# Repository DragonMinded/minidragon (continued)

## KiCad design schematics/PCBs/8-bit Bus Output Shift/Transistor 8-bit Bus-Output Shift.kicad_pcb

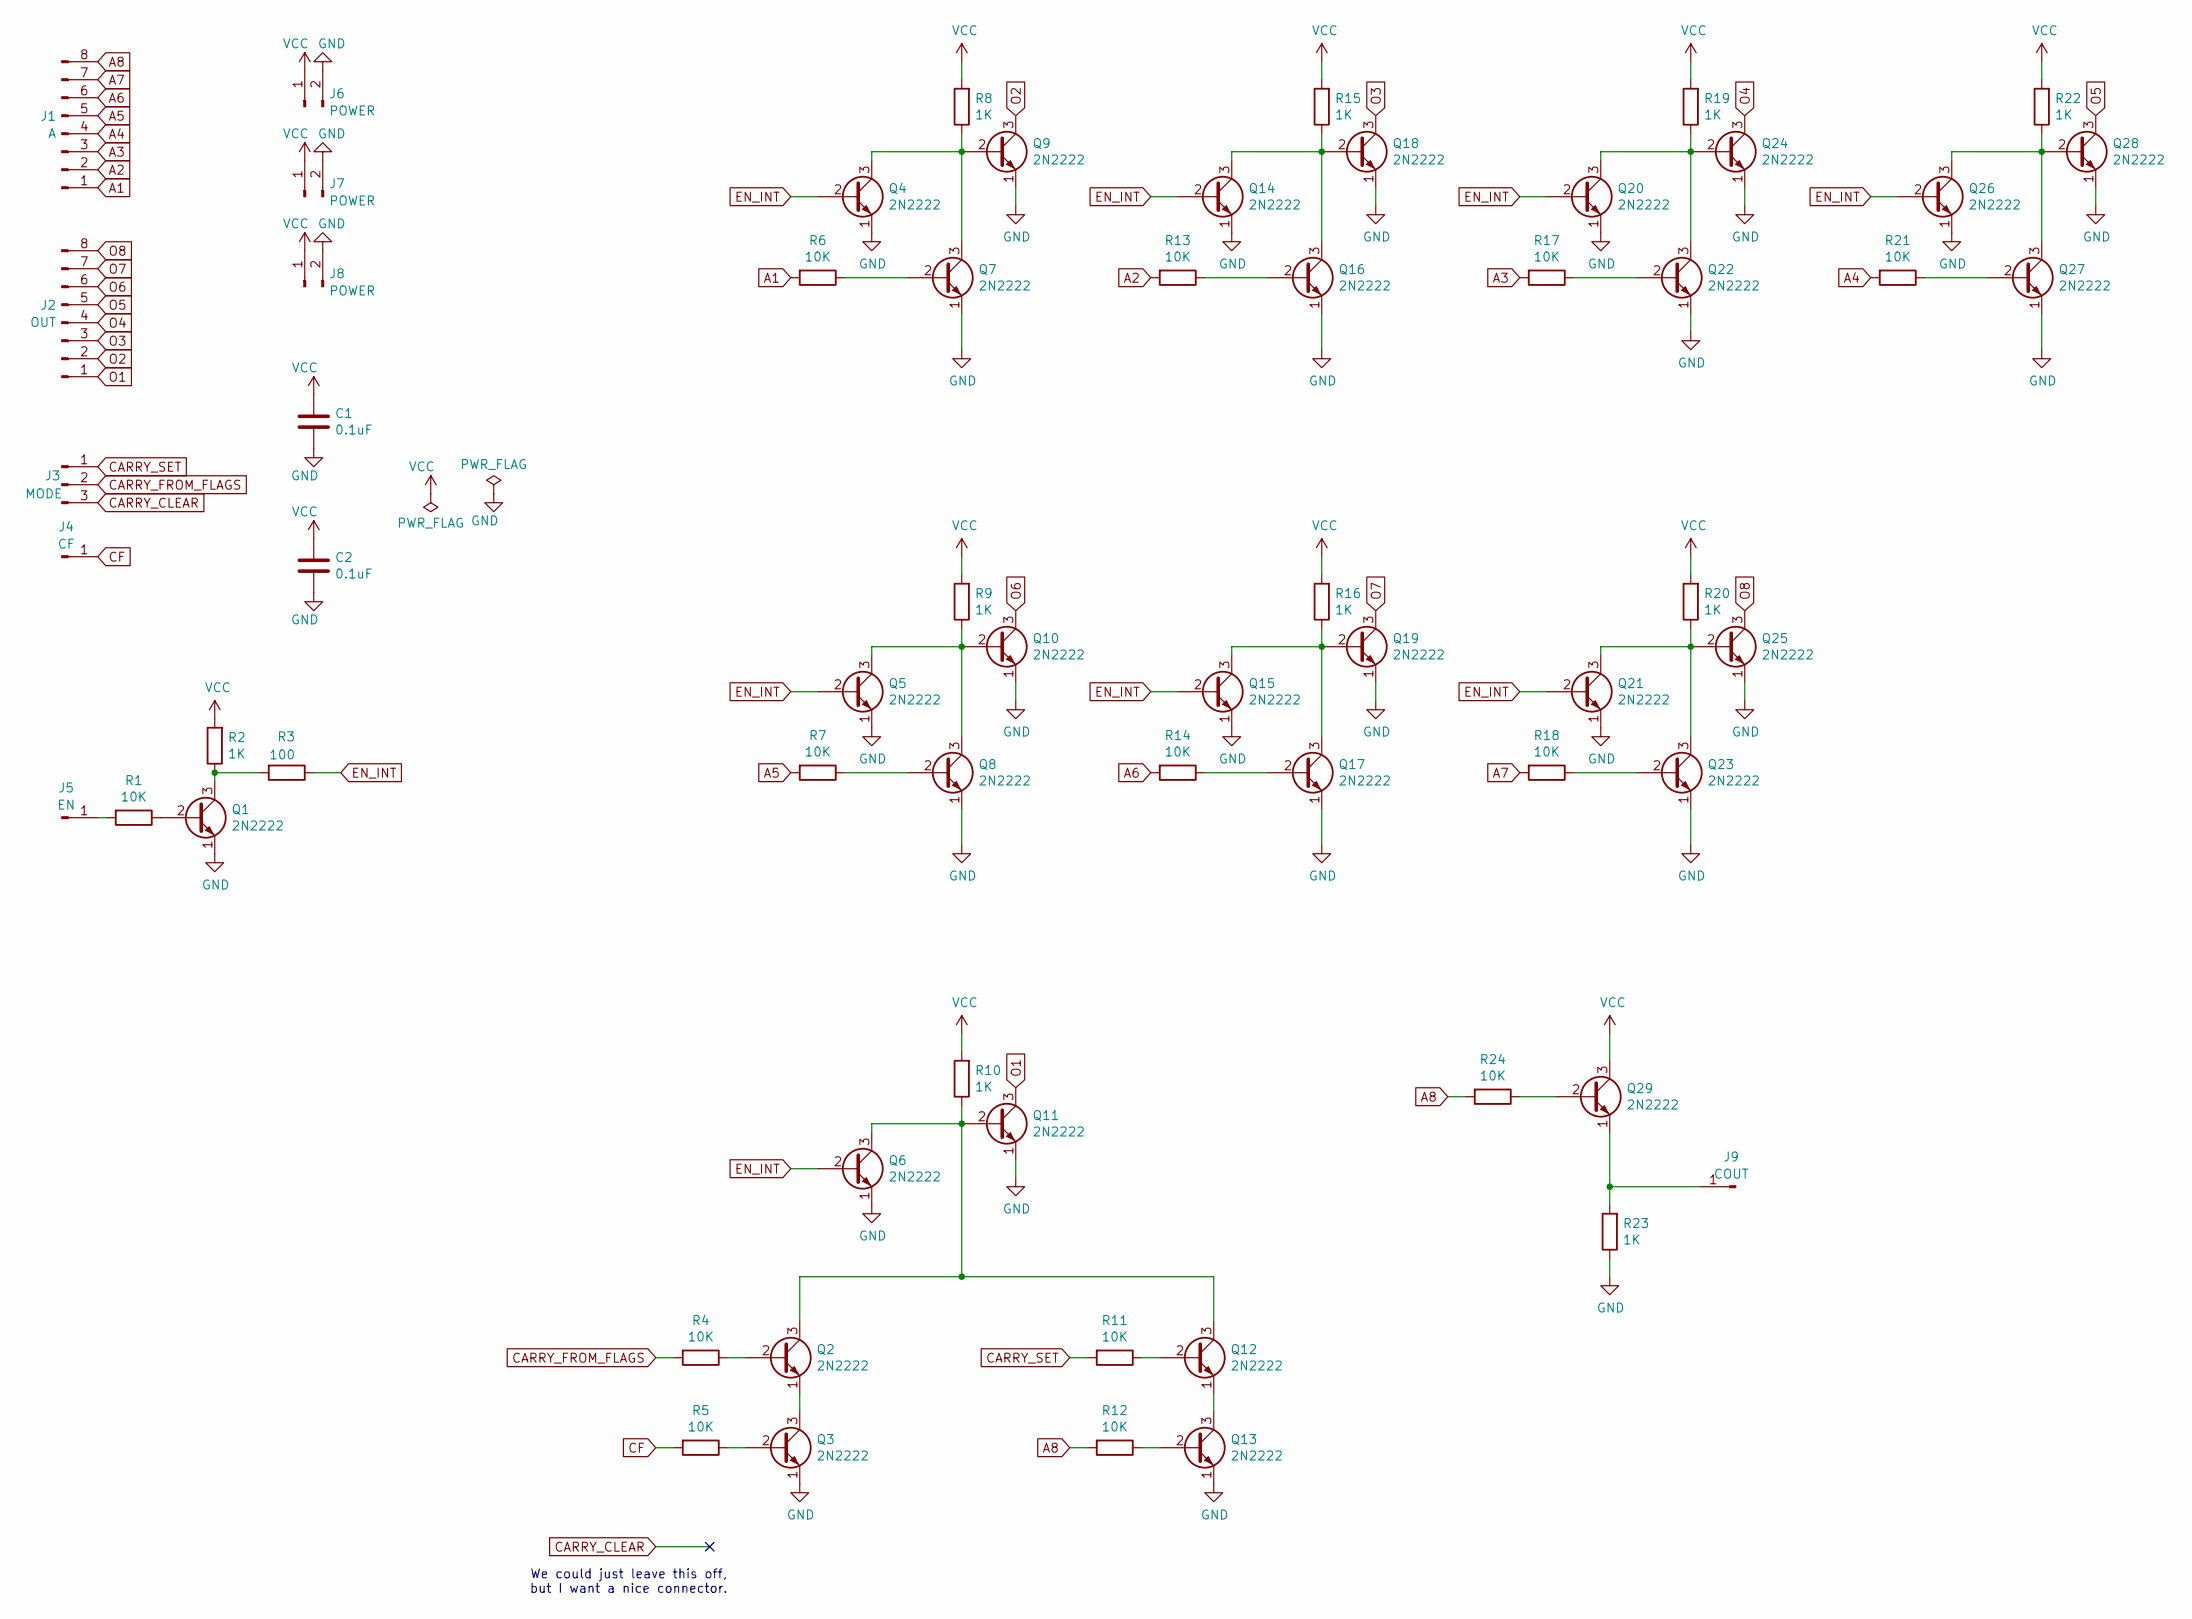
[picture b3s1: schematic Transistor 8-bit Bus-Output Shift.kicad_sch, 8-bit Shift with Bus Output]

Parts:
C1, C2: 0.1uF; C_Disc_D4.3mm_W1.9mm_P5.00mm
J1: A; PinHeader_1x08_P2.54mm_Vertical
J2: OUT; PinHeader_1x08_P2.54mm_Vertical
J3: MODE; PinHeader_1x03_P2.54mm_Vertical
J4: CF; PinHeader_1x01_P2.54mm_Vertical
J5: EN; PinHeader_1x01_P2.54mm_Vertical
J6, J7, J8: POWER; PinHeader_1x02_P2.54mm_Vertical
J9: COUT; PinHeader_1x01_P2.54mm_Vertical
Q1, Q2, Q3, Q4, Q5, Q6, Q7, Q8, Q9, Q10, Q11, Q12, Q13, Q14, Q15, Q16, Q17, Q18, Q19, Q20, Q21, Q22, Q23, Q24, Q25, Q26, Q27, Q28, Q29: 2N2222; TO-92_Inline
R1, R4, R5, R6, R7, R11, R12, R13, R14, R17, R18, R21, R24: 10K; R_Axial_DIN0309_L9.0mm_D3.2mm_P12.70mm_Horizontal
R2, R8, R9, R10, R15, R16, R19, R20, R22, R23: 1K; R_Axial_DIN0309_L9.0mm_D3.2mm_P12.70mm_Horizontal
R3: 100; R_Axial_DIN0309_L9.0mm_D3.2mm_P12.70mm_Horizontal

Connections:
A1: J1.1, R6.2
A2: J1.2, R13.2
A3: J1.3, R17.2
A4: J1.4, R21.2
A5: J1.5, R7.2
A6: J1.6, R14.2
A7: J1.7, R18.2
A8: J1.8, R12.2, R24.2
CARRY_CLEAR: J3.3
CARRY_FROM_FLAGS: J3.2, R4.2
CARRY_SET: J3.1, R11.2
CF: J4.1, R5.2
EN_INT: Q4.2 (B), Q5.2 (B), Q6.2 (B), Q14.2 (B), Q15.2 (B), Q20.2 (B), Q21.2 (B), Q26.2 (B), R3.1
GND: C1.2, C2.2, J6.2, J7.2, J8.2, Q1.1 (E), Q3.1 (E), Q4.1 (E), Q5.1 (E), Q6.1 (E), Q7.1 (E), Q8.1 (E), Q9.1 (E), Q10.1 (E), Q11.1 (E), Q13.1 (E), Q14.1 (E), Q15.1 (E), Q16.1 (E), Q17.1 (E), Q18.1 (E), Q19.1 (E), Q20.1 (E), Q21.1 (E), Q22.1 (E), Q23.1 (E), Q24.1 (E), Q25.1 (E), Q26.1 (E), Q27.1 (E), Q28.1 (E), R23.1
unnamed: J5.1, R1.2
unnamed: J9.1, Q29.1 (E), R23.2
unnamed: Q1.2 (B), R1.1
unnamed: Q1.3 (C), R2.1, R3.2
unnamed: Q2.2 (B), R4.1
unnamed: Q2.1 (E), Q3.3 (C)
unnamed: Q3.2 (B), R5.1
unnamed: Q4.3 (C), Q7.3 (C), Q9.2 (B), R8.1
unnamed: Q7.2 (B), R6.1
unnamed: Q8.2 (B), R7.1
unnamed: Q5.3 (C), Q8.3 (C), Q10.2 (B), R9.1
unnamed: Q2.3 (C), Q6.3 (C), Q11.2 (B), Q12.3 (C), R10.1
unnamed: Q12.2 (B), R11.1
unnamed: Q12.1 (E), Q13.3 (C)
unnamed: Q13.2 (B), R12.1
unnamed: Q14.3 (C), Q16.3 (C), Q18.2 (B), R15.1
unnamed: Q15.3 (C), Q17.3 (C), Q19.2 (B), R16.1
unnamed: Q16.2 (B), R13.1
unnamed: Q17.2 (B), R14.1
unnamed: Q20.3 (C), Q22.3 (C), Q24.2 (B), R19.1
unnamed: Q21.3 (C), Q23.3 (C), Q25.2 (B), R20.1
unnamed: Q22.2 (B), R17.1
unnamed: Q23.2 (B), R18.1
unnamed: Q26.3 (C), Q27.3 (C), Q28.2 (B), R22.1
unnamed: Q27.2 (B), R21.1
unnamed: Q29.2 (B), R24.1
O1: J2.1, Q11.3 (C)
O2: J2.2, Q9.3 (C)
O3: J2.3, Q18.3 (C)
O4: J2.4, Q24.3 (C)
O5: J2.5, Q28.3 (C)
O6: J2.6, Q10.3 (C)
O7: J2.7, Q19.3 (C)
O8: J2.8, Q25.3 (C)
VCC: C1.1, C2.1, J6.1, J7.1, J8.1, Q29.3 (C), R2.2, R8.2, R9.2, R10.2, R15.2, R16.2, R19.2, R20.2, R22.2

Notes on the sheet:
We could just leave this off, but I want a nice connector.

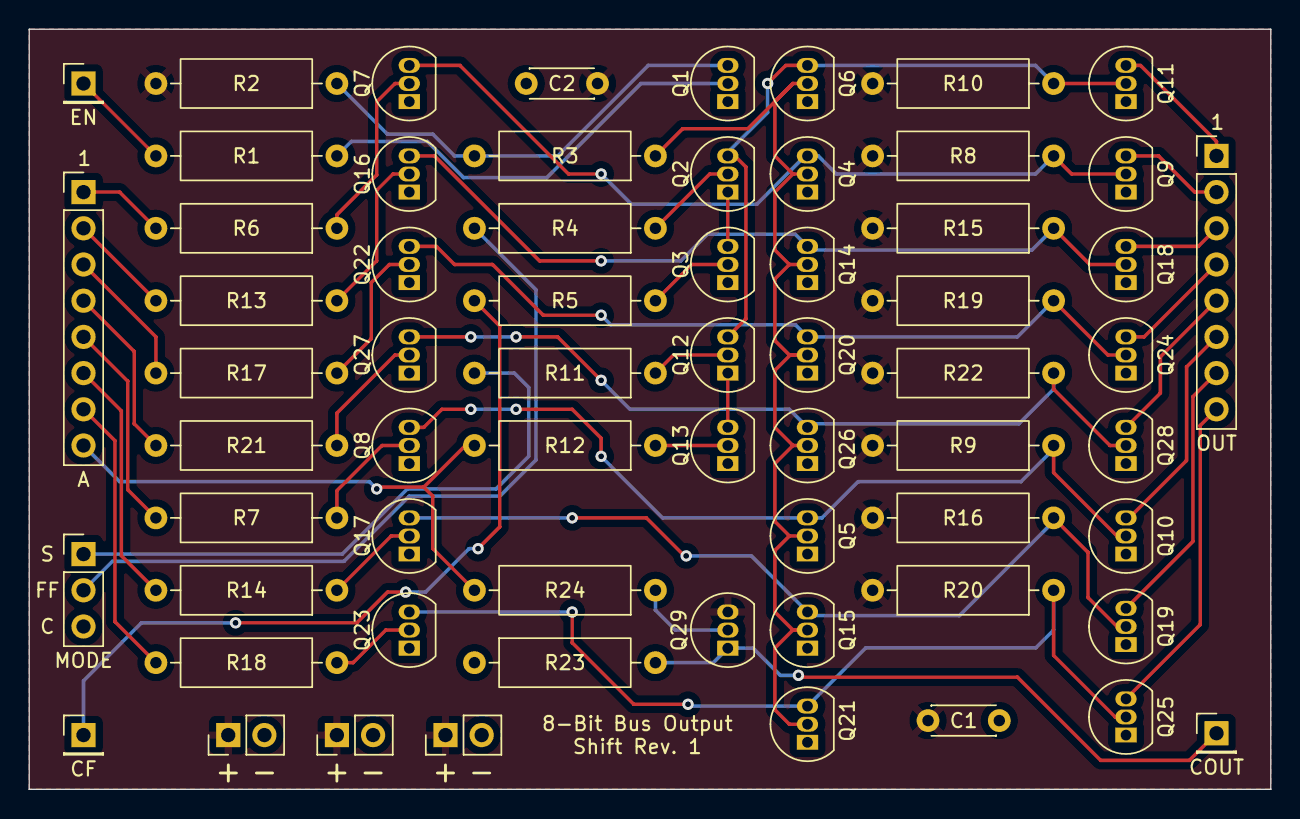
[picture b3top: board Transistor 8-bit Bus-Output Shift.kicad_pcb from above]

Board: 2 copper layers, 87.1 x 53.3 mm, 64 parts (0 on the bottom side), 48 nets.

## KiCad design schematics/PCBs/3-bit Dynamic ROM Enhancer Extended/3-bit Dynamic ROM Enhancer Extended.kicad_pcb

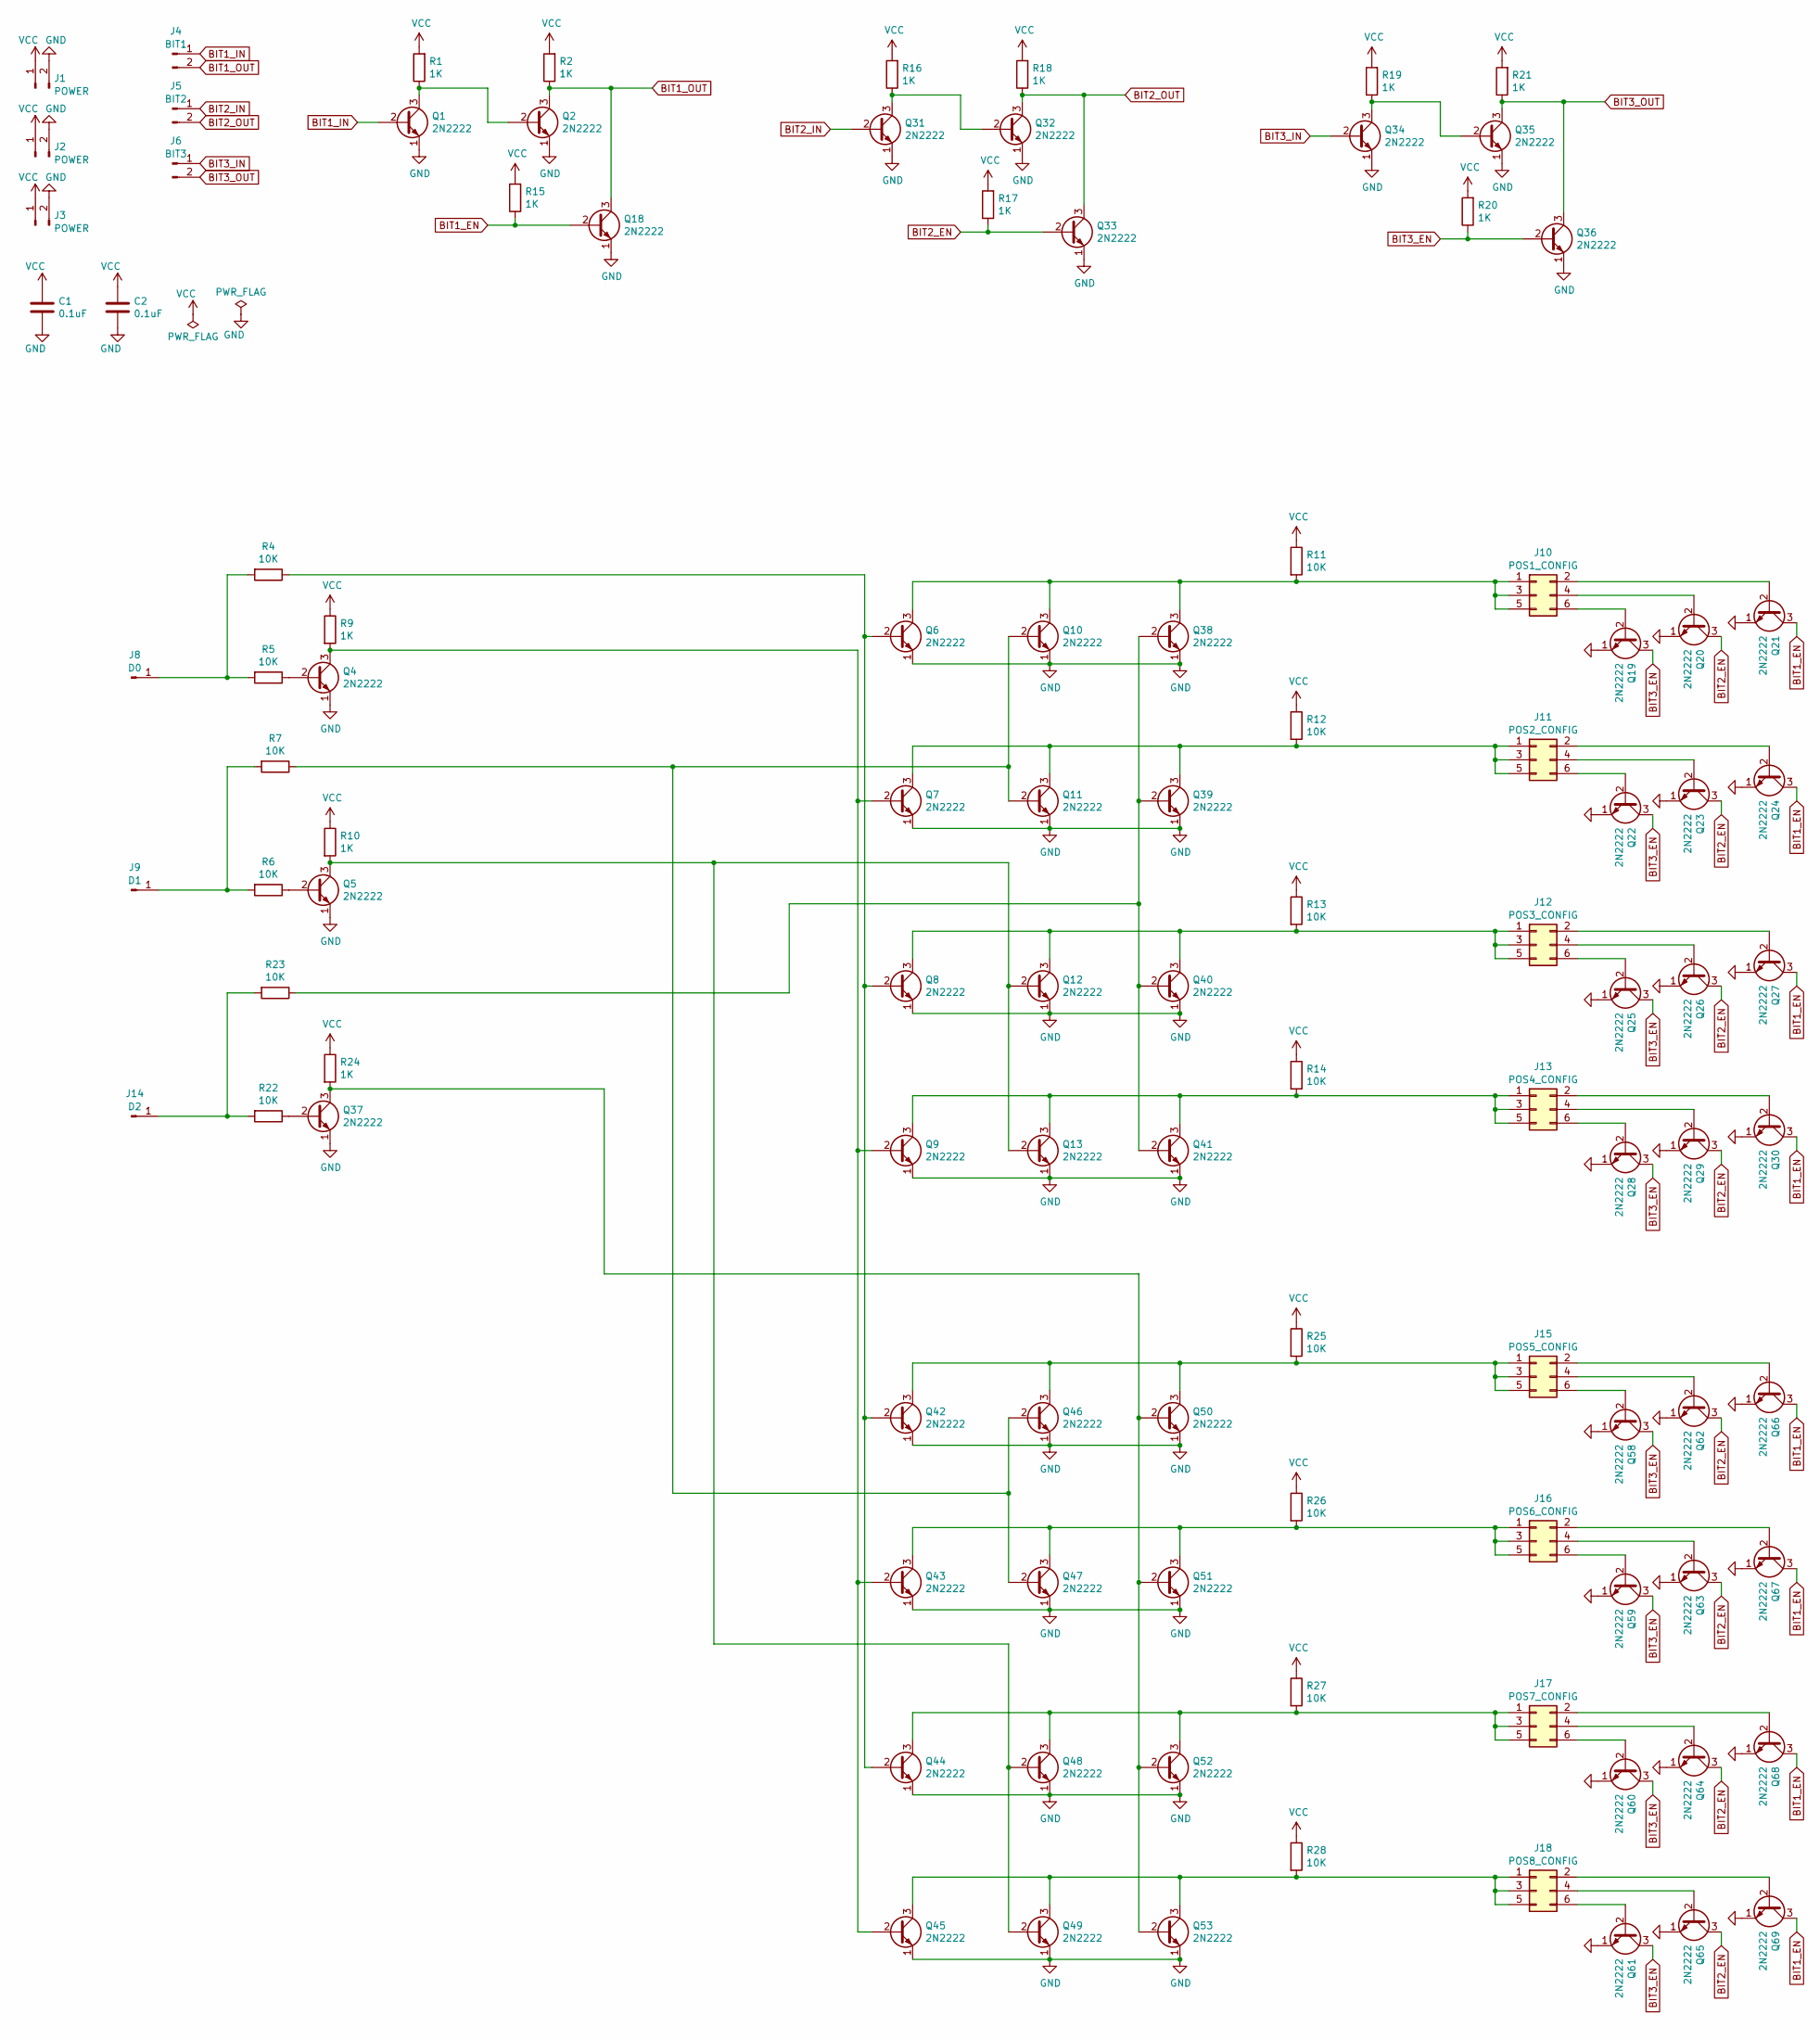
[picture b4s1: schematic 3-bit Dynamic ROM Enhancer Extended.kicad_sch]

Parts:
C1, C2: 0.1uF; C_Disc_D4.3mm_W1.9mm_P5.00mm
J1, J2, J3: POWER; PinHeader_1x02_P2.54mm_Vertical
J4: BIT1; PinHeader_1x02_P2.54mm_Vertical
J5: BIT2; PinHeader_1x02_P2.54mm_Vertical
J6: BIT3; PinHeader_1x02_P2.54mm_Vertical
J8: D0; PinHeader_1x01_P2.54mm_Vertical
J9: D1; PinHeader_1x01_P2.54mm_Vertical
J10: POS1_CONFIG; PinHeader_2x03_P2.54mm_Vertical
J11: POS2_CONFIG; PinHeader_2x03_P2.54mm_Vertical
J12: POS3_CONFIG; PinHeader_2x03_P2.54mm_Vertical
J13: POS4_CONFIG; PinHeader_2x03_P2.54mm_Vertical
J14: D2; PinHeader_1x01_P2.54mm_Vertical
J15: POS5_CONFIG; PinHeader_2x03_P2.54mm_Vertical
J16: POS6_CONFIG; PinHeader_2x03_P2.54mm_Vertical
J17: POS7_CONFIG; PinHeader_2x03_P2.54mm_Vertical
J18: POS8_CONFIG; PinHeader_2x03_P2.54mm_Vertical
Q1, Q2, Q4, Q5, Q6, Q7, Q8, Q9, Q10, Q11, Q12, Q13, Q18, Q19, Q20, Q21, Q22, Q23, Q24, Q25, Q26, Q27, Q28, Q29, Q30, Q31, Q32, Q33, Q34, Q35, Q36, Q37, Q38, Q39, Q40, Q41, Q42, Q43, Q44, Q45, Q46, Q47, Q48, Q49, Q50, Q51, Q52, Q53, Q58, Q59, Q60, Q61, Q62, Q63, Q64, Q65, Q66, Q67, Q68, Q69: 2N2222; TO-92_Inline
R1, R2, R9, R10, R15, R16, R17, R18, R19, R20, R21, R24: 1K; R_Axial_DIN0309_L9.0mm_D3.2mm_P12.70mm_Horizontal
R4, R5, R6, R7, R11, R12, R13, R14, R22, R23, R25, R26, R27, R28: 10K; R_Axial_DIN0309_L9.0mm_D3.2mm_P12.70mm_Horizontal

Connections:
BIT1_EN: Q18.2 (B), Q21.3 (C), Q24.3 (C), Q27.3 (C), Q30.3 (C), Q66.3 (C), Q67.3 (C), Q68.3 (C), Q69.3 (C), R15.1
BIT1_IN: J4.1, Q1.2 (B)
BIT1_OUT: J4.2, Q2.3 (C), Q18.3 (C), R2.1
BIT2_EN: Q20.3 (C), Q23.3 (C), Q26.3 (C), Q29.3 (C), Q33.2 (B), Q62.3 (C), Q63.3 (C), Q64.3 (C), Q65.3 (C), R17.1
BIT2_IN: J5.1, Q31.2 (B)
BIT2_OUT: J5.2, Q32.3 (C), Q33.3 (C), R18.1
BIT3_EN: Q19.3 (C), Q22.3 (C), Q25.3 (C), Q28.3 (C), Q36.2 (B), Q58.3 (C), Q59.3 (C), Q60.3 (C), Q61.3 (C), R20.1
BIT3_IN: J6.1, Q34.2 (B)
BIT3_OUT: J6.2, Q35.3 (C), Q36.3 (C), R21.1
GND: C1.2, C2.2, J1.2, J2.2, J3.2, Q1.1 (E), Q2.1 (E), Q4.1 (E), Q5.1 (E), Q6.1 (E), Q7.1 (E), Q8.1 (E), Q9.1 (E), Q10.1 (E), Q11.1 (E), Q12.1 (E), Q13.1 (E), Q18.1 (E), Q19.1 (E), Q20.1 (E), Q21.1 (E), Q22.1 (E), Q23.1 (E), Q24.1 (E), Q25.1 (E), Q26.1 (E), Q27.1 (E), Q28.1 (E), Q29.1 (E), Q30.1 (E), Q31.1 (E), Q32.1 (E), Q33.1 (E), Q34.1 (E), Q35.1 (E), Q36.1 (E), Q37.1 (E), Q38.1 (E), Q39.1 (E), Q40.1 (E), Q41.1 (E), Q42.1 (E), Q43.1 (E), Q44.1 (E), Q45.1 (E), Q46.1 (E), Q47.1 (E), Q48.1 (E), Q49.1 (E), Q50.1 (E), Q51.1 (E), Q52.1 (E), Q53.1 (E), Q58.1 (E), Q59.1 (E), Q60.1 (E), Q61.1 (E), Q62.1 (E), Q63.1 (E), Q64.1 (E), Q65.1 (E), Q66.1 (E), Q67.1 (E), Q68.1 (E), Q69.1 (E)
unnamed: J8.1, R4.2, R5.2
unnamed: J9.1, R6.2, R7.2
unnamed: J10.1, J10.3, J10.5, Q6.3 (C), Q10.3 (C), Q38.3 (C), R11.2
unnamed: J10.2, Q21.2 (B)
unnamed: J10.4, Q20.2 (B)
unnamed: J10.6, Q19.2 (B)
unnamed: J11.1, J11.3, J11.5, Q7.3 (C), Q11.3 (C), Q39.3 (C), R12.2
unnamed: J11.2, Q24.2 (B)
unnamed: J11.4, Q23.2 (B)
unnamed: J11.6, Q22.2 (B)
unnamed: J12.1, J12.3, J12.5, Q8.3 (C), Q12.3 (C), Q40.3 (C), R13.2
unnamed: J12.2, Q27.2 (B)
unnamed: J12.4, Q26.2 (B)
unnamed: J12.6, Q25.2 (B)
unnamed: J13.1, J13.3, J13.5, Q9.3 (C), Q13.3 (C), Q41.3 (C), R14.2
unnamed: J13.2, Q30.2 (B)
unnamed: J13.4, Q29.2 (B)
unnamed: J13.6, Q28.2 (B)
unnamed: J14.1, R22.2, R23.2
unnamed: J15.1, J15.3, J15.5, Q42.3 (C), Q46.3 (C), Q50.3 (C), R25.2
unnamed: J15.2, Q66.2 (B)
unnamed: J15.4, Q62.2 (B)
unnamed: J15.6, Q58.2 (B)
unnamed: J16.1, J16.3, J16.5, Q43.3 (C), Q47.3 (C), Q51.3 (C), R26.2
unnamed: J16.2, Q67.2 (B)
unnamed: J16.4, Q63.2 (B)
unnamed: J16.6, Q59.2 (B)
unnamed: J17.1, J17.3, J17.5, Q44.3 (C), Q48.3 (C), Q52.3 (C), R27.2
unnamed: J17.2, Q68.2 (B)
unnamed: J17.4, Q64.2 (B)
unnamed: J17.6, Q60.2 (B)
unnamed: J18.1, J18.3, J18.5, Q45.3 (C), Q49.3 (C), Q53.3 (C), R28.2
unnamed: J18.2, Q69.2 (B)
unnamed: J18.4, Q65.2 (B)
unnamed: J18.6, Q61.2 (B)
unnamed: Q1.3 (C), Q2.2 (B), R1.1
unnamed: Q4.2 (B), R5.1
unnamed: Q4.3 (C), Q7.2 (B), Q9.2 (B), Q43.2 (B), Q45.2 (B), R9.2
unnamed: Q5.2 (B), R6.1
unnamed: Q10.2 (B), Q11.2 (B), Q46.2 (B), Q47.2 (B), R7.1
unnamed: Q5.3 (C), Q12.2 (B), Q13.2 (B), Q48.2 (B), Q49.2 (B), R10.2
unnamed: Q31.3 (C), Q32.2 (B), R16.1
unnamed: Q34.3 (C), Q35.2 (B), R19.1
unnamed: Q37.2 (B), R22.1
unnamed: Q37.3 (C), Q50.2 (B), Q51.2 (B), Q52.2 (B), Q53.2 (B), R24.2
unnamed: Q38.2 (B), Q39.2 (B), Q40.2 (B), Q41.2 (B), R23.1
unnamed: Q6.2 (B), Q8.2 (B), Q42.2 (B), Q44.2 (B), R4.1
VCC: C1.1, C2.1, J1.1, J2.1, J3.1, R1.2, R2.2, R9.1, R10.1, R11.1, R12.1, R13.1, R14.1, R15.2, R16.2, R17.2, R18.2, R19.2, R20.2, R21.2, R24.1, R25.1, R26.1, R27.1, R28.1

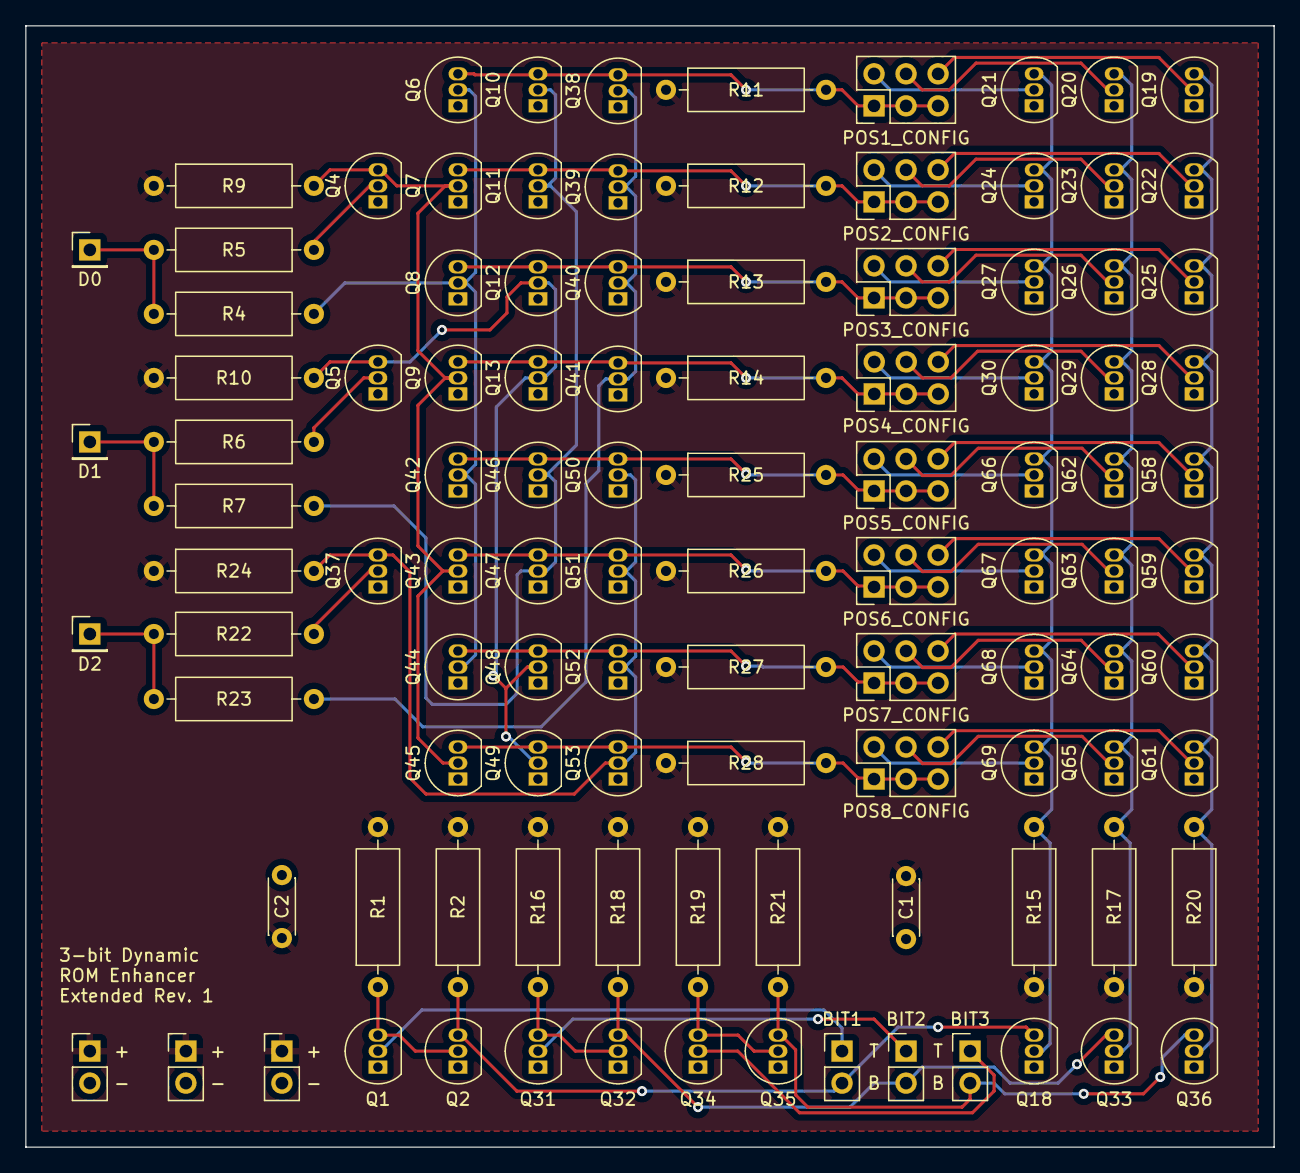
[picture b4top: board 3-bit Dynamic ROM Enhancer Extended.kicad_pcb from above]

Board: 2 copper layers, 99.1 x 89.0 mm, 105 parts (0 on the bottom side), 58 nets.

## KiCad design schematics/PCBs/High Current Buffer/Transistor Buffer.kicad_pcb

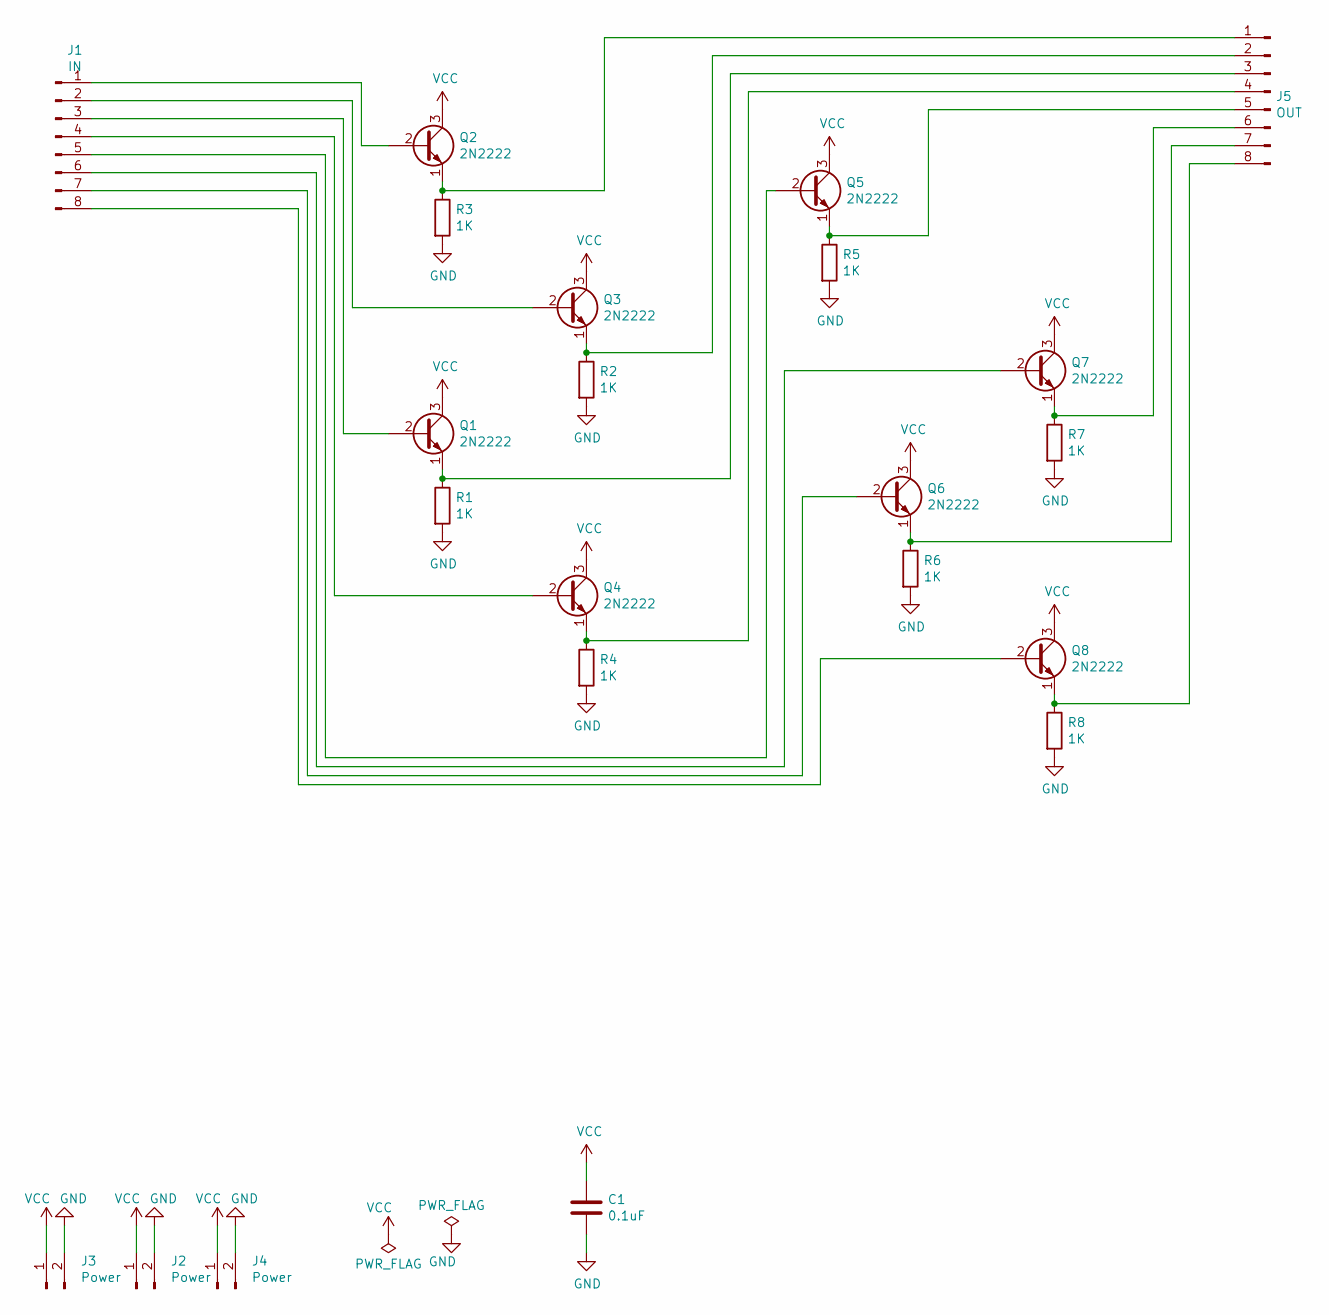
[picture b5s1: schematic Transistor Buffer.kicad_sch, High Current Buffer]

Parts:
C1: 0.1uF; C_Disc_D4.3mm_W1.9mm_P5.00mm
J1: IN; PinHeader_1x08_P2.54mm_Vertical
J2, J3, J4: Power; PinHeader_1x02_P2.54mm_Vertical
J5: OUT; PinHeader_1x08_P2.54mm_Vertical
Q1, Q2, Q3, Q4, Q5, Q6, Q7, Q8: 2N2222; TO-92_Inline
R1, R2, R3, R4, R5, R6, R7, R8: 1K; R_Axial_DIN0309_L9.0mm_D3.2mm_P12.70mm_Horizontal

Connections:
GND: C1.2, J2.2, J3.2, J4.2, R1.2, R2.2, R3.2, R4.2, R5.2, R6.2, R7.2, R8.2
unnamed: J1.1, Q2.2 (B)
unnamed: J1.2, Q3.2 (B)
unnamed: J1.3, Q1.2 (B)
unnamed: J1.4, Q4.2 (B)
unnamed: J1.5, Q5.2 (B)
unnamed: J1.6, Q7.2 (B)
unnamed: J1.7, Q6.2 (B)
unnamed: J1.8, Q8.2 (B)
unnamed: J5.1, Q2.1 (E), R3.1
unnamed: J5.2, Q3.1 (E), R2.1
unnamed: J5.3, Q1.1 (E), R1.1
unnamed: J5.4, Q4.1 (E), R4.1
unnamed: J5.5, Q5.1 (E), R5.1
unnamed: J5.6, Q7.1 (E), R7.1
unnamed: J5.7, Q6.1 (E), R6.1
unnamed: J5.8, Q8.1 (E), R8.1
VCC: C1.1, J2.1, J3.1, J4.1, Q1.3 (C), Q2.3 (C), Q3.3 (C), Q4.3 (C), Q5.3 (C), Q6.3 (C), Q7.3 (C), Q8.3 (C)

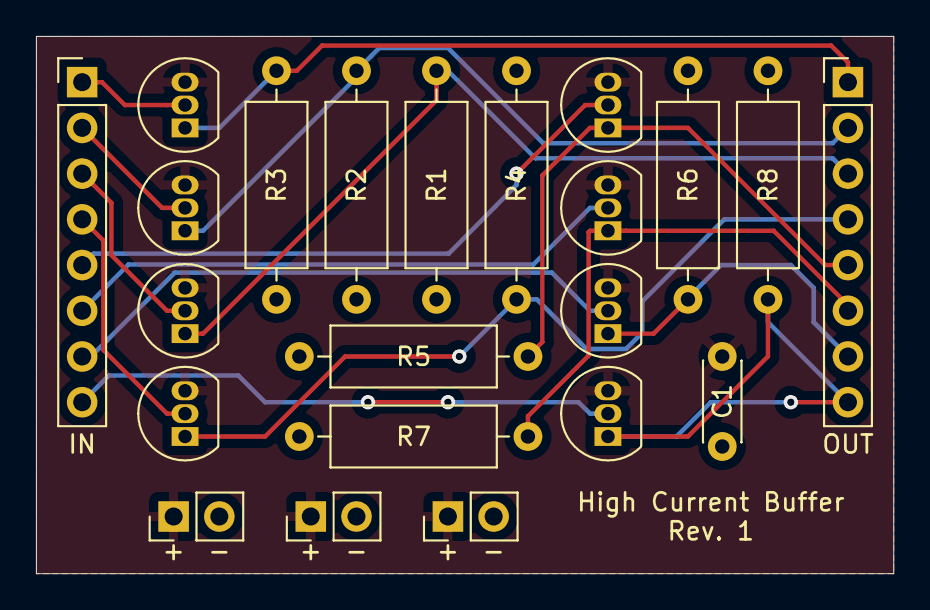
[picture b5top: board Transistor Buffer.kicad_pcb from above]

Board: 2 copper layers, 47.6 x 29.8 mm, 22 parts (0 on the bottom side), 18 nets.

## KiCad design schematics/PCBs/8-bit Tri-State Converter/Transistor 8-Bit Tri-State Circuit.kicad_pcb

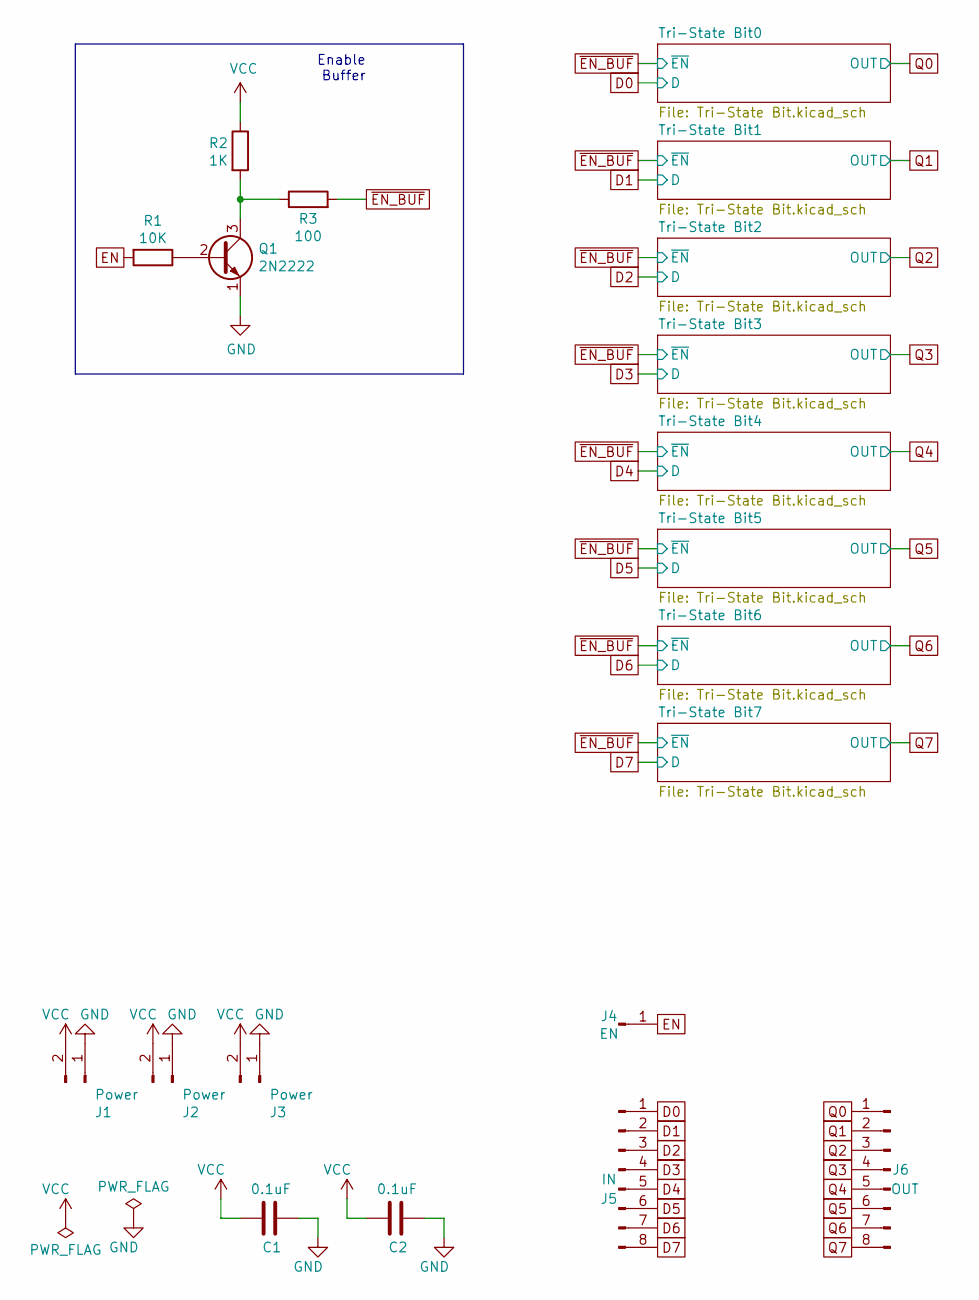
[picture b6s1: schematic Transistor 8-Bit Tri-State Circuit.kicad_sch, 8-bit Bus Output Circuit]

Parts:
C1, C2: 0.1uF; C_Disc_D4.3mm_W1.9mm_P5.00mm
J1, J2, J3: Power; PinHeader_1x02_P2.54mm_Vertical
J4: EN; PinHeader_1x01_P2.54mm_Vertical
J5: IN; PinHeader_1x08_P2.54mm_Vertical
J6: OUT; PinHeader_1x08_P2.54mm_Vertical
Q1: 2N2222; TO-92_Inline
R1: 10K; R_Axial_DIN0309_L9.0mm_D3.2mm_P12.70mm_Horizontal
R2: 1K; R_Axial_DIN0309_L9.0mm_D3.2mm_P12.70mm_Horizontal
R3: 100; R_Axial_DIN0309_L9.0mm_D3.2mm_P12.70mm_Horizontal

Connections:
D0: J5.1; also elsewhere on the board
D1: J5.2; also elsewhere on the board
D2: J5.3; also elsewhere on the board
D3: J5.4; also elsewhere on the board
D4: J5.5; also elsewhere on the board
D5: J5.6; also elsewhere on the board
D6: J5.7; also elsewhere on the board
D7: J5.8; also elsewhere on the board
EN: J4.1, R1.2
GND: C1.1, C2.1, J1.1, J2.1, J3.1, Q1.1 (E); also elsewhere on the board
unnamed: Q1.2 (B), R1.1
unnamed: Q1.3 (C), R2.2, R3.1
Q0: J6.1; also elsewhere on the board
Q1: J6.2; also elsewhere on the board
Q2: J6.3; also elsewhere on the board
Q3: J6.4; also elsewhere on the board
Q4: J6.5; also elsewhere on the board
Q5: J6.6; also elsewhere on the board
Q6: J6.7; also elsewhere on the board
Q7: J6.8; also elsewhere on the board
VCC: C1.2, C2.2, J1.2, J2.2, J3.2, R2.1; also elsewhere on the board
~EN_BUF: R3.2; also elsewhere on the board

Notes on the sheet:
Enable Buffer
